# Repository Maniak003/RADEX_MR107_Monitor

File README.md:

<!DOCTYPE html>
<html lang="en" data-color-mode="auto" data-light-theme="light" data-dark-theme="dark">
  <head>
    <meta charset="utf-8">
  </head>
    <body class="logged-in env-production page-responsive page-blob" style="word-wrap: break-word;">
      <p> RADEX_MR107_Monitor.<br><b></p>

    </body>
</html>

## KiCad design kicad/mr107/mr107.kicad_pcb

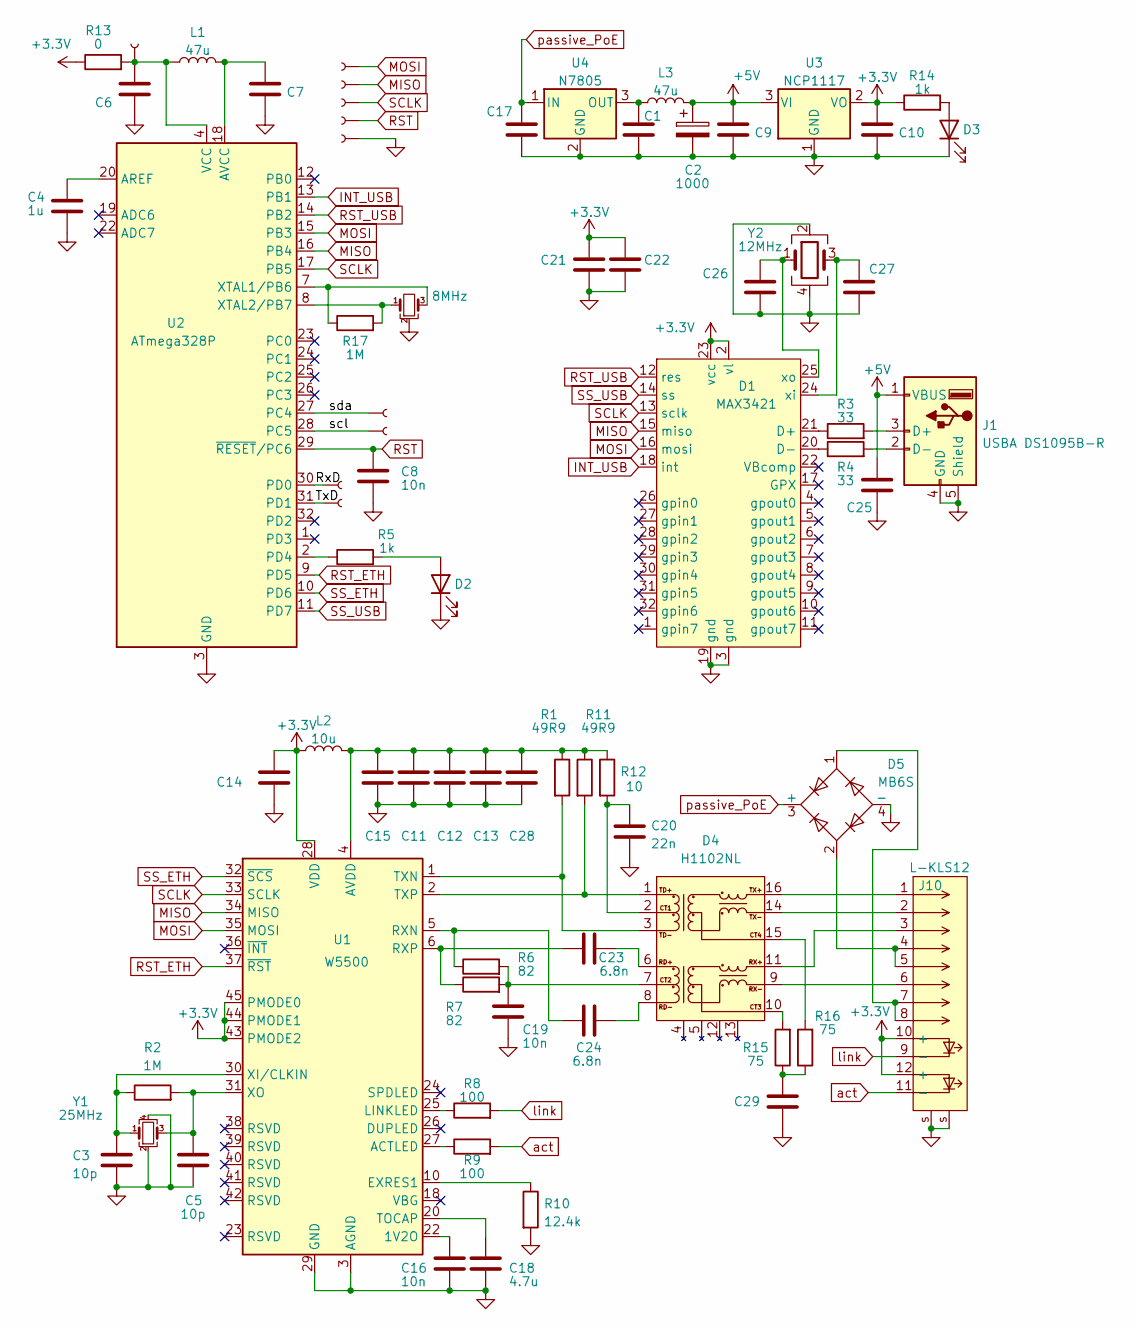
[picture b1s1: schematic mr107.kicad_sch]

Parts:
C1, C9, C10, C17, C25: 10u; C_0805_2012Metric
C2: 1000; CP_EIA-7343-15_Kemet-W
C3, C5: 10p; C_0402_1005Metric
C4, C6, C11, C12, C13, C14, C15, C21, C22: 1u; C_0603_1608Metric
C7: 10u; C_0603_1608Metric
C8: 10n; C_0603_1608Metric
C16, C19: 10n; C_0402_1005Metric
C18: 4.7u; C_0402_1005Metric
C20: 22n; C_0402_1005Metric
C23, C24: 6.8n; C_0402_1005Metric
C26, C27: 8p; C_0603_1608Metric
C28: 1u; C_0402_1005Metric
C29: 1n 2kV; C_1206_3216Metric
D1: MAX3421; PQFP-32_5x5mm_P0.5mm
D2, D3: LED; LED_0603_1608Metric
D4: H1102NL; H1102N
D5: MB6S; TO-269AA
J1: USBA DS1095B-R; USB_A_CONNFLY_DS1095-WNR0
J2: RxD; conn_mini
J3, J11, J12: mosi; conn_mini
J4: miso; conn_mini
J5: sclk; conn_mini
J6: reset; conn_mini
J7: gnd; conn_mini
J8: TxD; conn_mini
J9: PW; conn_mini
J10: L-KLS12; KLS12-108
L1, L3: 47u; L_0805_2012Metric
L2: 10u; L_0805_2012Metric
R1, R11: 49R9; R_0402_1005Metric
R2, R17: 1M; R_0402_1005Metric
R3, R4: 33; R_0603_1608Metric
R5, R14: 1k; R_0603_1608Metric
R6, R7: 82; R_0402_1005Metric
R8, R9: 100; R_0603_1608Metric
R10: 12.4k; R_0402_1005Metric
R12: 10; R_0402_1005Metric
R13: 0; R_0603_1608Metric
R15, R16: 75; R_0603_1608Metric
U1: W5500; LQFP-48_7x7mm_P0.5mm
U2: ATmega328P; TQFP-32_7x7mm_P0.8mm
U3: NCP1117; SOT-223-3_TabPin2
U4: N7805; TO-220-3_Vertical
Y1: 25MHz; Crystal_SMD_3225-4Pin_3.2x2.5mm
Y2: 12MHz; Crystal_SMD_0603-4Pin_6.0x3.5mm
Y3: 8MHz; Resonator_SMD_Murata_CSTxExxV-3Pin_3.0x1.1mm

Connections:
+3.3V: C10.1, C14.1, C21.1, C22.1, D1.2 (vl), D1.23 (vcc), J10.10 (+), J10.12 (+), L2.1, R13.1, R14.1, U1.28 (VDD), U1.43 (PMODE2), U1.44 (PMODE1), U1.45 (PMODE0), U3.2 (VO)
+5V: C2.1, C9.1, C25.1, J1.1 (VBUS), L3.2, U3.3 (VI)
/RxD: J2.1, U2.30 (PD0)
/TxD: J8.1, U2.31 (PD1)
/scl: J12.1, U2.28 (PC5)
/sda: J11.1, U2.27 (PC4)
GND: C1.2, C2.2, C3.2, C4.2, C5.2, C6.2, C7.2, C8.2, C9.2, C10.2, C11.2, C12.2, C13.2, C14.2, C15.2, C16.2, C17.2, C18.2, C19.2, C20.2, C21.2, C22.2, C25.2, C26.2, C27.2, C28.2, C29.2, D1.3 (gnd), D1.19 (gnd), D2.1 (K), D3.1 (K), D5.4 (-), J1.4 (GND), J1.5 (Shield), J7.1, J10.s, R10.2, U1.3 (AGND), U1.9 (AGND), U1.14 (AGND), U1.16 (AGND), U1.19 (AGND), U1.29 (GND), U1.48 (AGND), U2.3 (GND), U2.5 (GND), U2.21 (GND), U3.1 (GND), U4.2 (GND), Y1.2, Y1.4, Y2.2, Y2.4, Y3.2
INT_USB: D1.18 (int), U2.13 (PB1)
MISO: D1.15 (miso), J4.1, U1.34 (MISO), U2.16 (PB4)
MOSI: D1.16 (mosi), J3.1, U1.35 (MOSI), U2.15 (PB3)
unnamed: C1.1, L3.1, U4.3 (OUT)
unnamed: C3.1, R2.1, U1.30 (XI/CLKIN), Y1.1
unnamed: C4.1, U2.20 (AREF)
unnamed: C5.1, R2.2, U1.31 (XO), Y1.3
unnamed: C6.1, J9.1, L1.1, R13.2, U2.4 (VCC), U2.6 (VCC)
unnamed: C7.1, L1.2, U2.18 (AVCC)
unnamed: C11.1, C12.1, C13.1, C15.1, C28.1, L2.2, R1.1, R11.1, R12.1, U1.4 (AVDD), U1.8 (AVDD), U1.11 (AVDD), U1.15 (AVDD), U1.17 (AVDD), U1.21 (AVDD)
unnamed: C16.1, U1.22 (1V2O)
unnamed: C18.1, U1.20 (TOCAP)
unnamed: C19.1, D4.7, R6.2, R7.2
unnamed: C20.1, D4.2, R12.2
unnamed: C23.1, R7.1, U1.6 (RXP)
unnamed: C23.2, D4.6
unnamed: C24.1, R6.1, U1.5 (RXN)
unnamed: C24.2, D4.8
unnamed: C26.1, D1.25 (xo), Y2.1
unnamed: C27.1, D1.24 (xi), Y2.3
unnamed: C29.1, R15.1, R16.1
unnamed: D1.20 (D-), R4.1
unnamed: D1.21 (D+), R3.1
unnamed: D2.2 (A), R5.2
unnamed: D3.2 (A), R14.2
unnamed: D4.1, R11.2, U1.2 (TXP)
unnamed: D4.3, R1.2, U1.1 (TXN)
unnamed: D4.9, J10.6
unnamed: D4.10, R15.2
unnamed: D4.11, J10.3
unnamed: D4.14, J10.2
unnamed: D4.15, R16.2
unnamed: D4.16, J10.1
unnamed: D5.1, J10.7, J10.8
unnamed: D5.2, J10.4, J10.5
unnamed: J1.2 (D-), R4.2
unnamed: J1.3 (D+), R3.2
unnamed: R5.1, U2.2 (PD4)
unnamed: R8.1, U1.25 (LINKLED)
unnamed: R9.1, U1.27 (ACTLED)
unnamed: R10.1, U1.10 (EXRES1)
unnamed: R17.1, U2.7 (XTAL1/PB6), Y3.3
unnamed: R17.2, U2.8 (XTAL2/PB7), Y3.1
RST: C8.1, J6.1, U2.29 (~RESET/PC6)
RST_ETH: U1.37 (~RST), U2.9 (PD5)
RST_USB: D1.12 (res), U2.14 (PB2)
SCLK: D1.13 (sclk), J5.1, U1.33 (SCLK), U2.17 (PB5)
SS_ETH: U1.32 (~SCS), U2.10 (PD6)
SS_USB: D1.14 (ss), U2.11 (PD7)
act: J10.11 (-), R9.2
link: J10.9 (-), R8.2
passive_PoE: C17.1, D5.3 (+), U4.1 (IN)

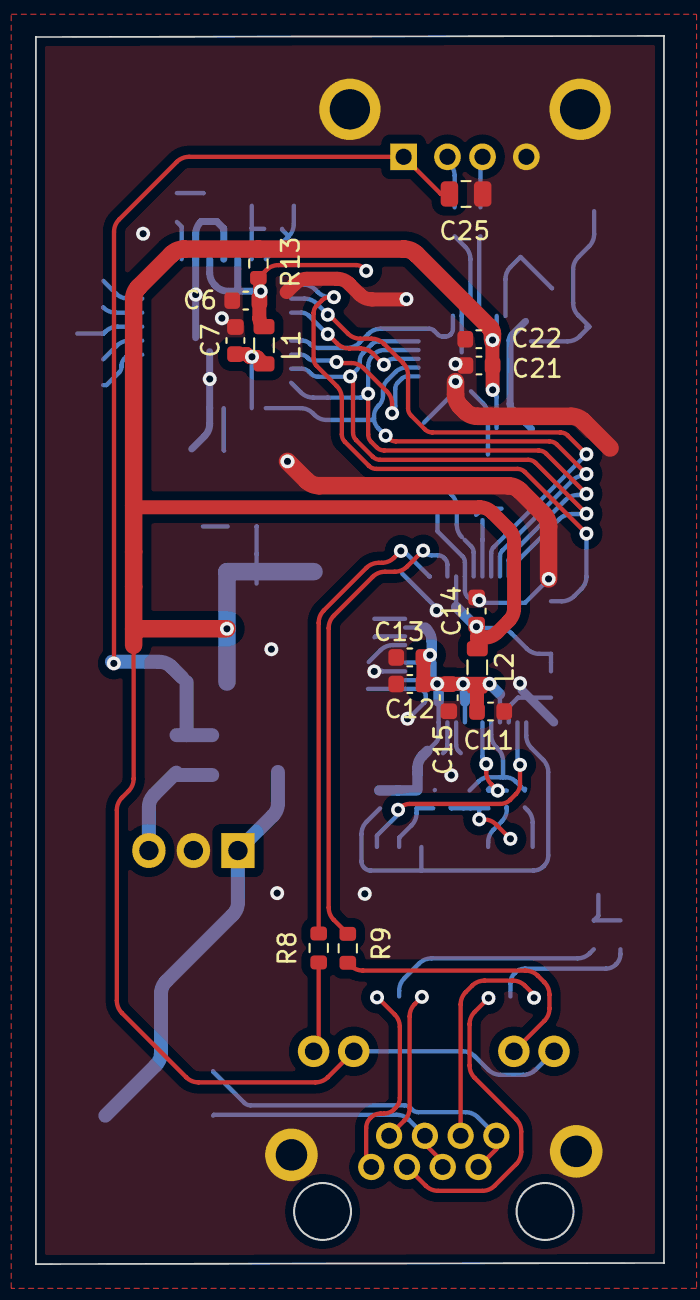
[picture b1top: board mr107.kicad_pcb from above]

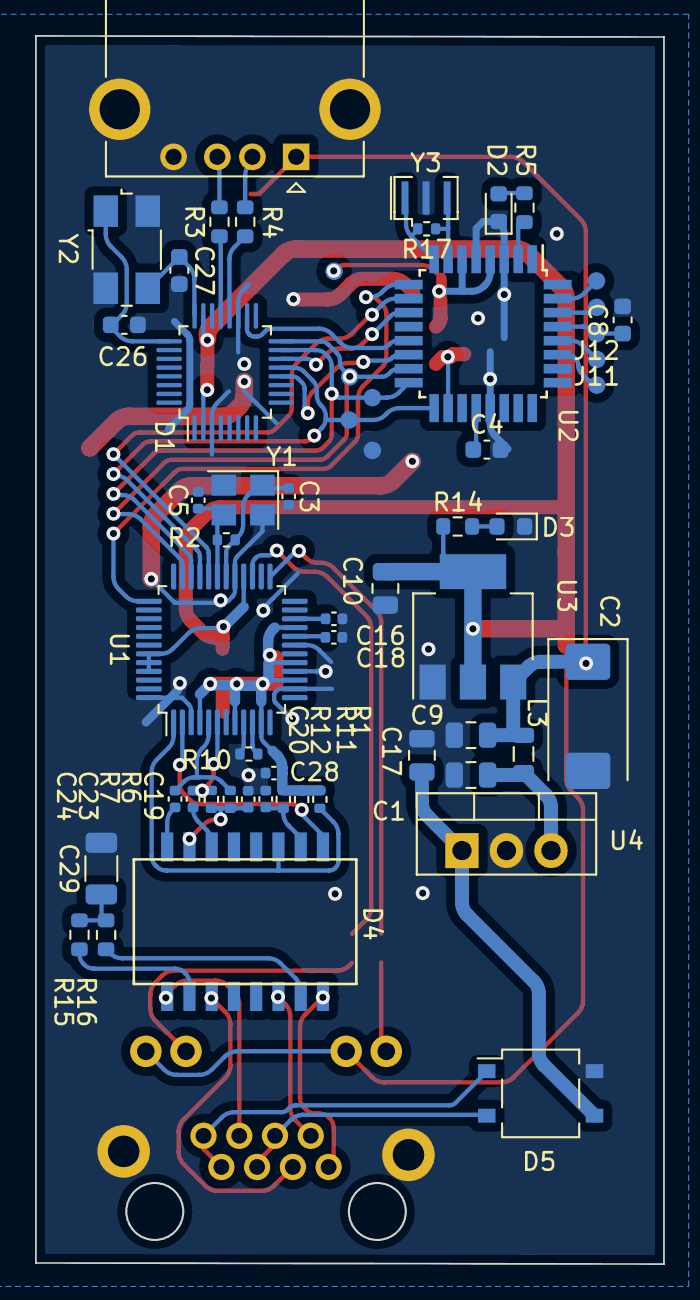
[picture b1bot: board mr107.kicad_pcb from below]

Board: 2 copper layers, 35.8 x 70.1 mm, 73 parts (58 on the bottom side), 59 nets.

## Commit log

2023-12-15 изменено: AVR/mr107_/mr107_.ino новый файл: kicad/mr107/bom/ibom.html изменено: kicad/mr107/gerber/Border.gbr изменено: kicad/mr107/gerber/Bottom.gbr изменено: kicad/mr107/gerber/MaskBottom.gbr измен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
2023-12-15 изменено: kicad/mr107/bom/ibom.html
2023-12-18 переименовано: AVR/mr107_/W5100_Layout_Guide.pdf -> Documents/W5100_Layout_Guide.pdf переименовано: AVR/mr107_/W5100_Ref_sch_MAG_R2.1.pdf -> Documents/W5100_Ref_sch_MAG_R2.1.pdf
2023-12-18 новый файл: kicad/mr107_802.3af/bom/ibom.html новый файл: kicad/mr107_802.3af/fp-info-cache новый файл: kicad/mr107_802.3af/gerber/Border.gbr новый файл: kicad/mr107_802.3af/gerber/Bottom.gbr новый ф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
2023-12-18 удалено: kicad/mr107_802.3af/gerber/Border.gbr удалено: kicad/mr107_802.3af/gerber/Bottom.gbr удалено: kicad/mr107_802.3af/gerber/MaskBottom.gbr удалено: kicad/mr107_802.3af/gerber/MaskTop.gbr удален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
2023-12-18 изменено: kicad/mr107_802.3af/bom/ibom.html
2023-12-19 удалено: kicad/mr107_802.3af/mr107-backups/mr107-2023-12-09_163958.zip удалено: kicad/mr107_802.3af/mr107-backups/mr107-2023-12-18_154055.zip изменено: kicad/mr107_802.3af/mr107.kicad_prl изменено: k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
2023-12-29 изменено: kicad/mr107/bom/ibom.html удалено: kicad/mr107/gerber/Border.gbr удалено: kicad/mr107/gerber/Bottom.gbr удалено: kicad/mr107/gerber/MaskBottom.gbr удалено: kicad/mr107/gerber/MaskTop.gbr уд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
2023-12-31 новый файл: AVR/library/Ethernet/AUTHORS новый файл: AVR/library/Ethernet/README.adoc новый файл: AVR/library/Ethernet/examples/AdvancedChatServer/AdvancedChatServer.ino новый файл: AVR/library/Ether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
2024-01-16 изменено: AVR/mr107_/mr107_.ino удалено: kicad/mr107/mr107-backups/mr107-2023-12-07_190314.zip
2024-01-16 изменено: AVR/mr107_/mr107_.ino.eightanaloginputs.hex изменено: AVR/mr107_/mr107_.ino.with_bootloader.eightanaloginputs.hex
2024-02-27 изменено: AVR/mr107_/mr107_.ino
2024-02-27 удалено: AVR/mr107_/mr107_.ino.eightanaloginputs.hex удалено: AVR/mr107_/mr107_.ino.with_bootloader.eightanaloginputs.hex
2024-02-27 новый файл: Documents/IMG_20240113_131636.jpg новый файл: Documents/IMG_20240113_173617.jpg новый файл: Documents/img_thermal_1705140843939.jpg
2024-03-08 изменено: AVR/mr107_/mr107_.ino изменено: kicad/mr107_802.3af/mr107.kicad_prl
2024-07-30 изменено: AVR/mr107_/mr107_.ino удалено: kicad/mr107/mr107-backups/mr107-2023-12-09_164959.zip удалено: kicad/mr107/mr107-backups/mr107-2023-12-09_165959.zip удалено: kicad/mr107/mr107-backups/mr107-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
2024-07-30 новый файл: AVR/mr107_EEPROMCFG/mr107_EEPROMCFG.ino
2024-07-30 новый файл: FreeCAD/mr107_box.FCStd новый файл: FreeCAD/mr107_box.stl новый файл: FreeCAD/mr107_cover.FCStd новый файл: FreeCAD/mr107_cover.stl
2024-07-30 изменено: AVR/mr107_EEPROMCFG/mr107_EEPROMCFG.ino
2024-07-31 изменено: AVR/mr107_/write-avr.sh изменено: AVR/mr107_/write-avr.sh~ изменено: AVR/mr107_EEPROMCFG/mr107_EEPROMCFG.ino изменено: kicad/mr107_802.3af/bom/ibom.html
2024-08-02 изменено: AVR/mr107_EEPROMCFG/mr107_EEPROMCFG.ino изменено: kicad/mr107/mr107.kicad_sch
2024-08-02 изменено: AVR/mr107_EEPROMCFG/mr107_EEPROMCFG.ino удалено: kicad/mr107/mr107-backups/mr107-2023-12-11_173003.zip
2024-08-02 удалено: kicad/mr107/mr107-backups/mr107-2023-12-12_103509.zip удалено: kicad/mr107/mr107-backups/mr107-2023-12-12_104452.zip удалено: kicad/mr107/mr107-backups/mr107-2023-12-12_105008.zip удалено: k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
2024-08-30 удалено: kicad/mr107/mr107-backups/mr107-2023-12-12_110331.zip
2024-09-03 изменено: kicad/mr107/gerber/mr107.zip изменено: kicad/mr107/mr107.kicad_pcb изменено: kicad/mr107/mr107.kicad_sch
2024-09-04 изменено: AVR/mr107_EEPROMCFG/mr107_EEPROMCFG.ino новый файл: Documents/N78.PDF новый файл: Documents/ttl_uart_cfg.png новый файл: Documents/ttl_uart_out.png
2024-09-04 новый файл: Documents/ttl_uart_res.png
2024-09-06 изменено: kicad/mr107/fp-info-cache изменено: kicad/mr107/mr107.kicad_pcb изменено: kicad/mr107/mr107.kicad_prl изменено: kicad/mr107/mr107.kicad_sch
2024-09-06 новый файл: FreeCAD/bmp280Case.FCStd новый файл: FreeCAD/bmp280Case.stl
